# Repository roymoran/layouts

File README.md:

## Layouts

### USB C Power, UJC-HP-3-SMT-TR

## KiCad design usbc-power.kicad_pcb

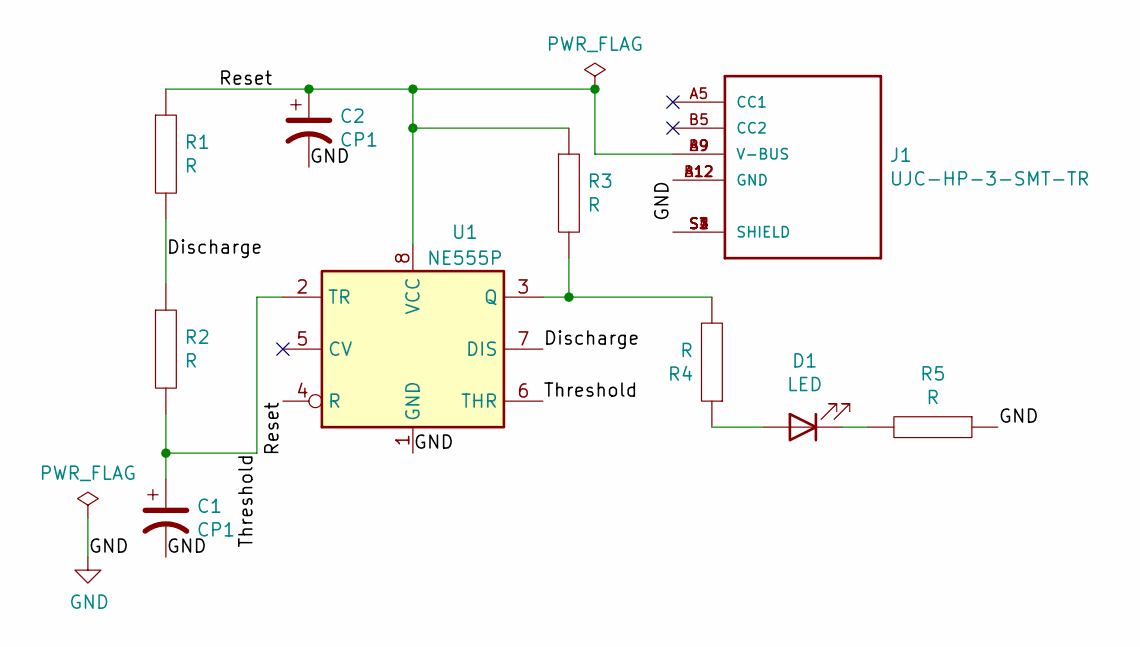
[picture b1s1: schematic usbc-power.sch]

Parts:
C1, C2: CP1; CP_Radial_D4.0mm_P1.50mm
D1: LED; LED_D5.0mm
J1: UJC-HP-3-SMT-TR; CUI_UJC-HP-3-SMT-TR
R1, R2, R3, R4, R5: R; R_Axial_DIN0207_L6.3mm_D2.5mm_P2.54mm_Vertical
U1: NE555P; DIP-8_W7.62mm

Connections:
/Discharge: R1.2, R2.1, U1.7 (DIS)
/Reset: C2.1, J1.A9 (V-BUS), J1.B9 (V-BUS), R1.1, R3.1, U1.4 (R), U1.8 (VCC)
/Threshold: C1.1, R2.2, U1.2 (TR), U1.6 (THR)
GND: C1.2, C2.2, J1.A12 (GND), J1.B12 (GND), R5.1, U1.1 (GND)
unnamed: D1.1 (K), R5.2
unnamed: D1.2 (A), R4.1
unnamed: J1.S1 (SHIELD), J1.S2 (SHIELD), J1.S3 (SHIELD), J1.S4 (SHIELD)
unnamed: R3.2, R4.2, U1.3 (Q)

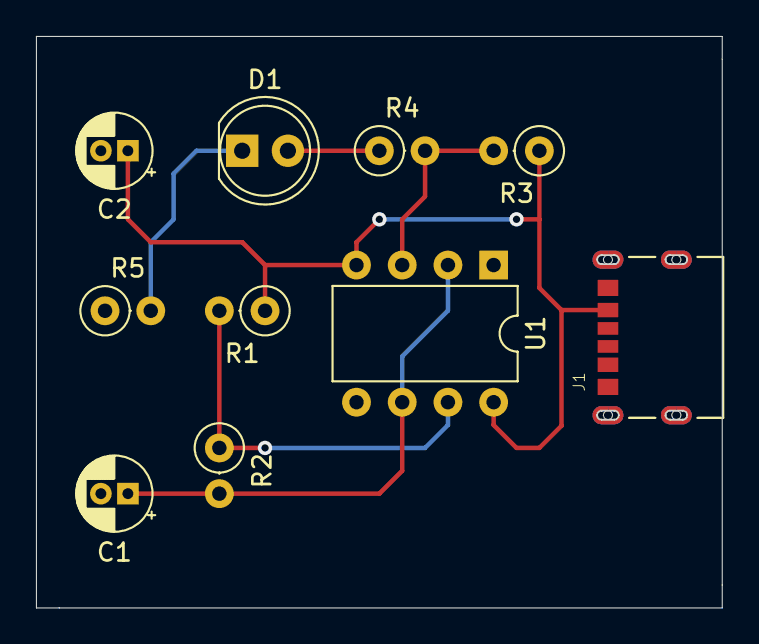
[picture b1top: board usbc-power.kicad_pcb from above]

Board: 2 copper layers, 38.0 x 31.7 mm, 10 parts (0 on the bottom side), 8 nets.

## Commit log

2020-10-01 inital usb c board layout
2020-10-01 include readme
2020-10-01 modify pcb layout, add tracks and ground plane
2020-10-03 add current limiting resistor, generate gerbers
